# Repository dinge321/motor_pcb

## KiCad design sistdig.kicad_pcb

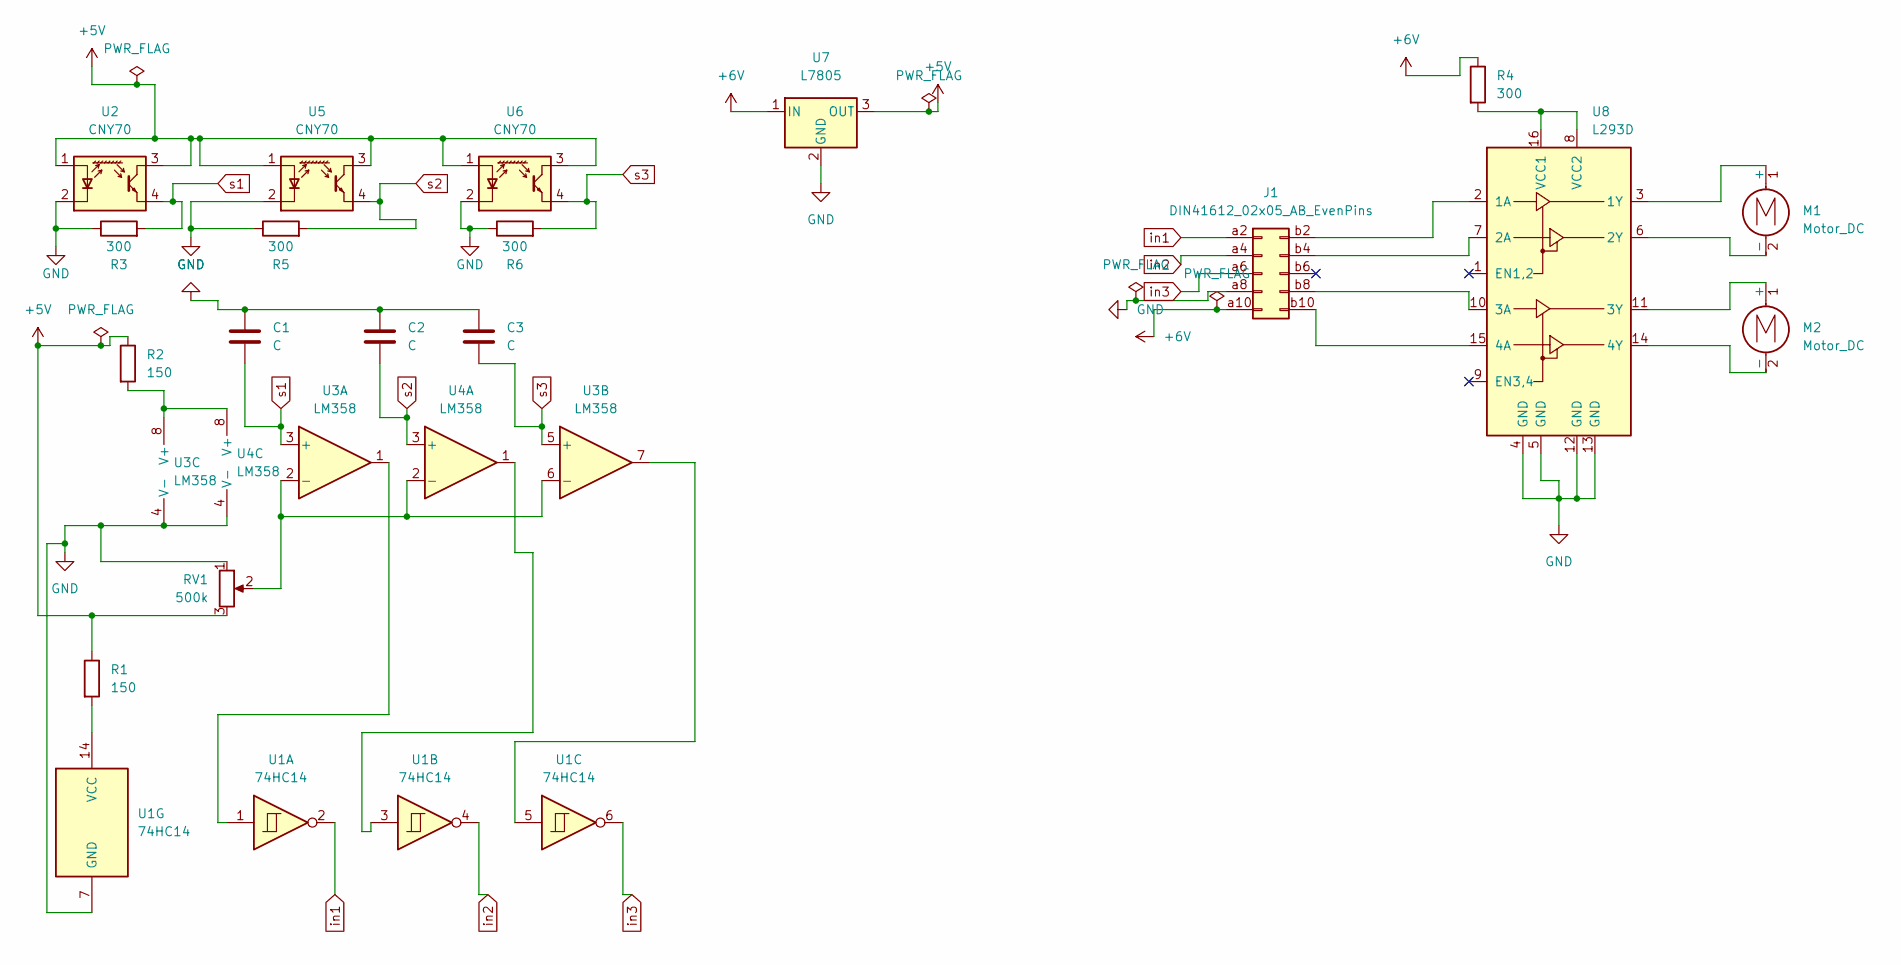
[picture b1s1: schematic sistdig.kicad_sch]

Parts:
C1, C2, C3: C; C_Disc_D3.0mm_W1.6mm_P2.50mm
J1: DIN41612_02x05_AB_EvenPins; DIN41612_B3_2x5_Female_Vertical_THT
M1, M2: Motor_DC; PinHeader_1x02_P2.54mm_Vertical
R1, R2: 150; R_LDR_4.9x4.2mm_P2.54mm_Vertical
R3, R4, R5, R6: 300; R_LDR_4.9x4.2mm_P2.54mm_Vertical
RV1: 500k; Potentiometer_Alps_RK09Y11_Single_Horizontal
U1: 74HC14; DIP-14_W7.62mm
U2, U5, U6: CNY70; Vishay_CNY70
U3, U4: LM358; DIP-8_W7.62mm
U7: L7805; TO-220-3_Horizontal_TabDown
U8: L293D; DIP-16_W7.62mm

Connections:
+5V: R1.1, R2.1, RV1.3, U2.1 (A), U2.3 (C), U5.1 (A), U5.3 (C), U6.1 (A), U6.3 (C), U7.3 (OUT)
+6V: J1.a10, R4.1, U7.1 (IN)
GND: C1.1, C2.1, C3.1, J1.a8, R3.1, R5.1, R6.1, RV1.1, U1.7 (GND), U2.2 (K), U3.4 (V-), U4.4 (V-), U5.2 (K), U6.2 (K), U7.2 (GND), U8.4 (GND), U8.5 (GND), U8.12 (GND), U8.13 (GND)
unnamed: J1.b2, U8.2 (1A)
unnamed: J1.b4, U8.7 (2A)
unnamed: J1.b8, U8.10 (3A)
unnamed: J1.b10, U8.15 (4A)
unnamed: M1.1 (+), U8.3 (1Y)
unnamed: M1.2 (-), U8.6 (2Y)
unnamed: M2.1 (+), U8.11 (3Y)
unnamed: M2.2 (-), U8.14 (4Y)
unnamed: R1.2, U1.14 (VCC)
unnamed: R2.2, U3.8 (V+), U4.8 (V+)
unnamed: R4.2, U8.8 (VCC2), U8.16 (VCC1)
unnamed: RV1.2, U3.2 (-), U3.6 (-), U4.2 (-)
unnamed: U1.1, U3.1
unnamed: U1.3, U4.1
unnamed: U1.5, U3.7
in1: J1.a2, U1.2
in2: J1.a4, U1.4
in3: J1.a6, U1.6
s1: C1.2, R3.2, U2.4 (E), U3.3 (+)
s2: C2.2, R5.2, U4.3 (+), U5.4 (E)
s3: C3.2, R6.2, U3.5 (+), U6.4 (E)

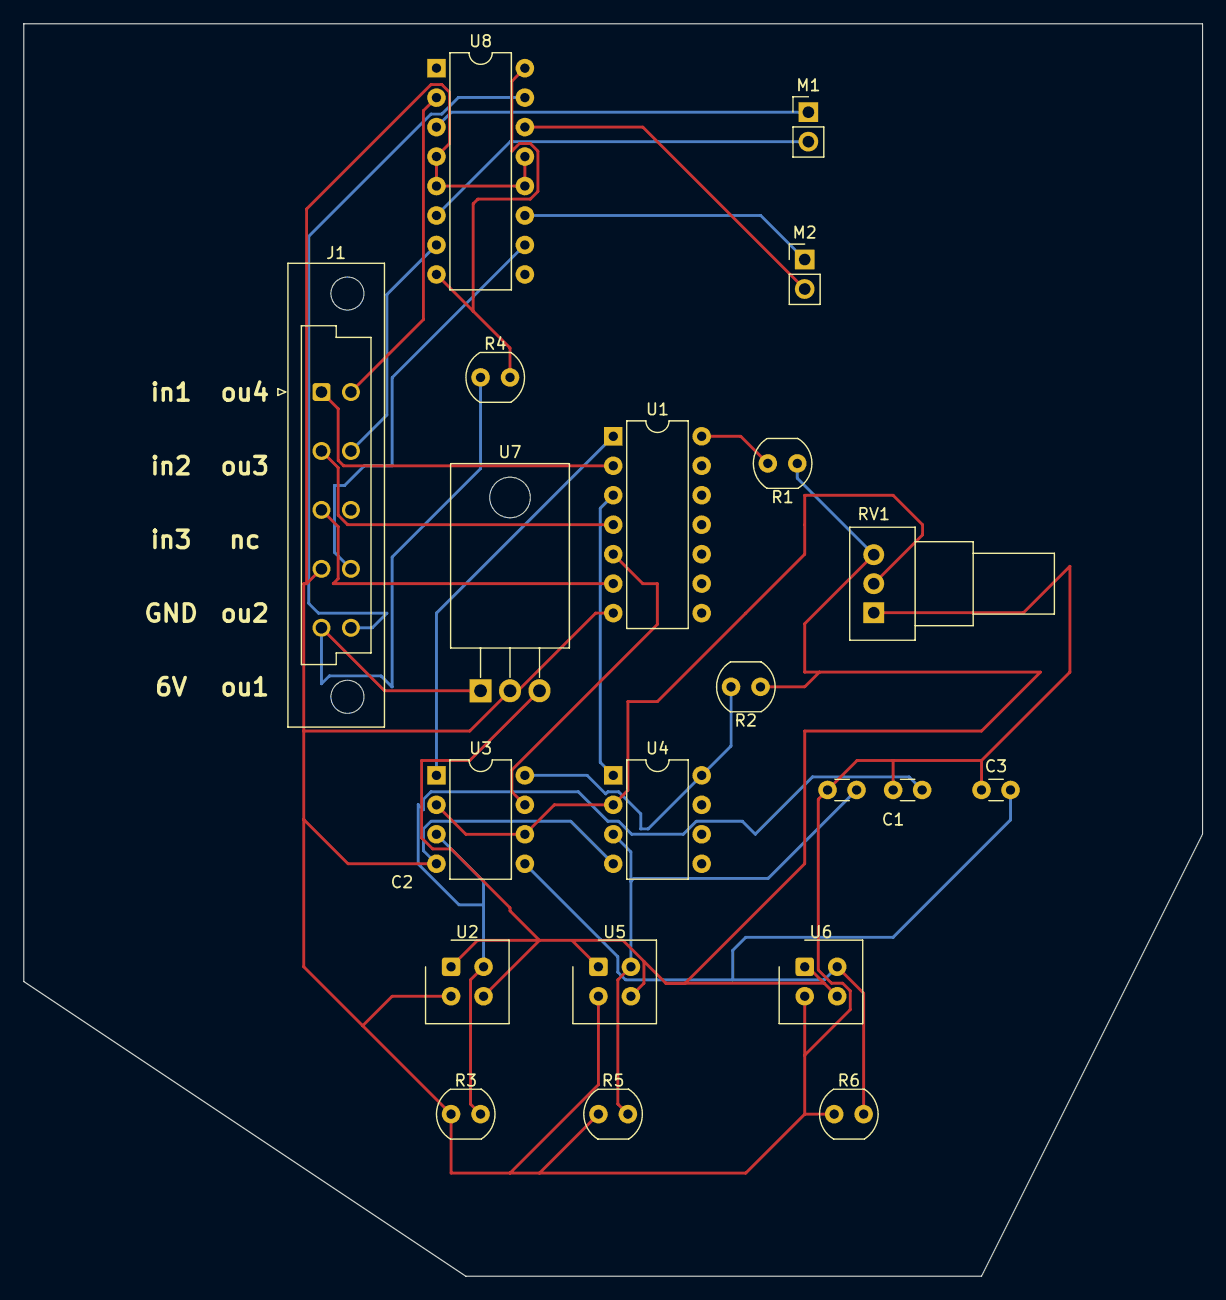
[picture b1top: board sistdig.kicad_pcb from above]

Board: 2 copper layers, 101.6 x 107.9 mm, 21 parts (0 on the bottom side), 24 nets.
